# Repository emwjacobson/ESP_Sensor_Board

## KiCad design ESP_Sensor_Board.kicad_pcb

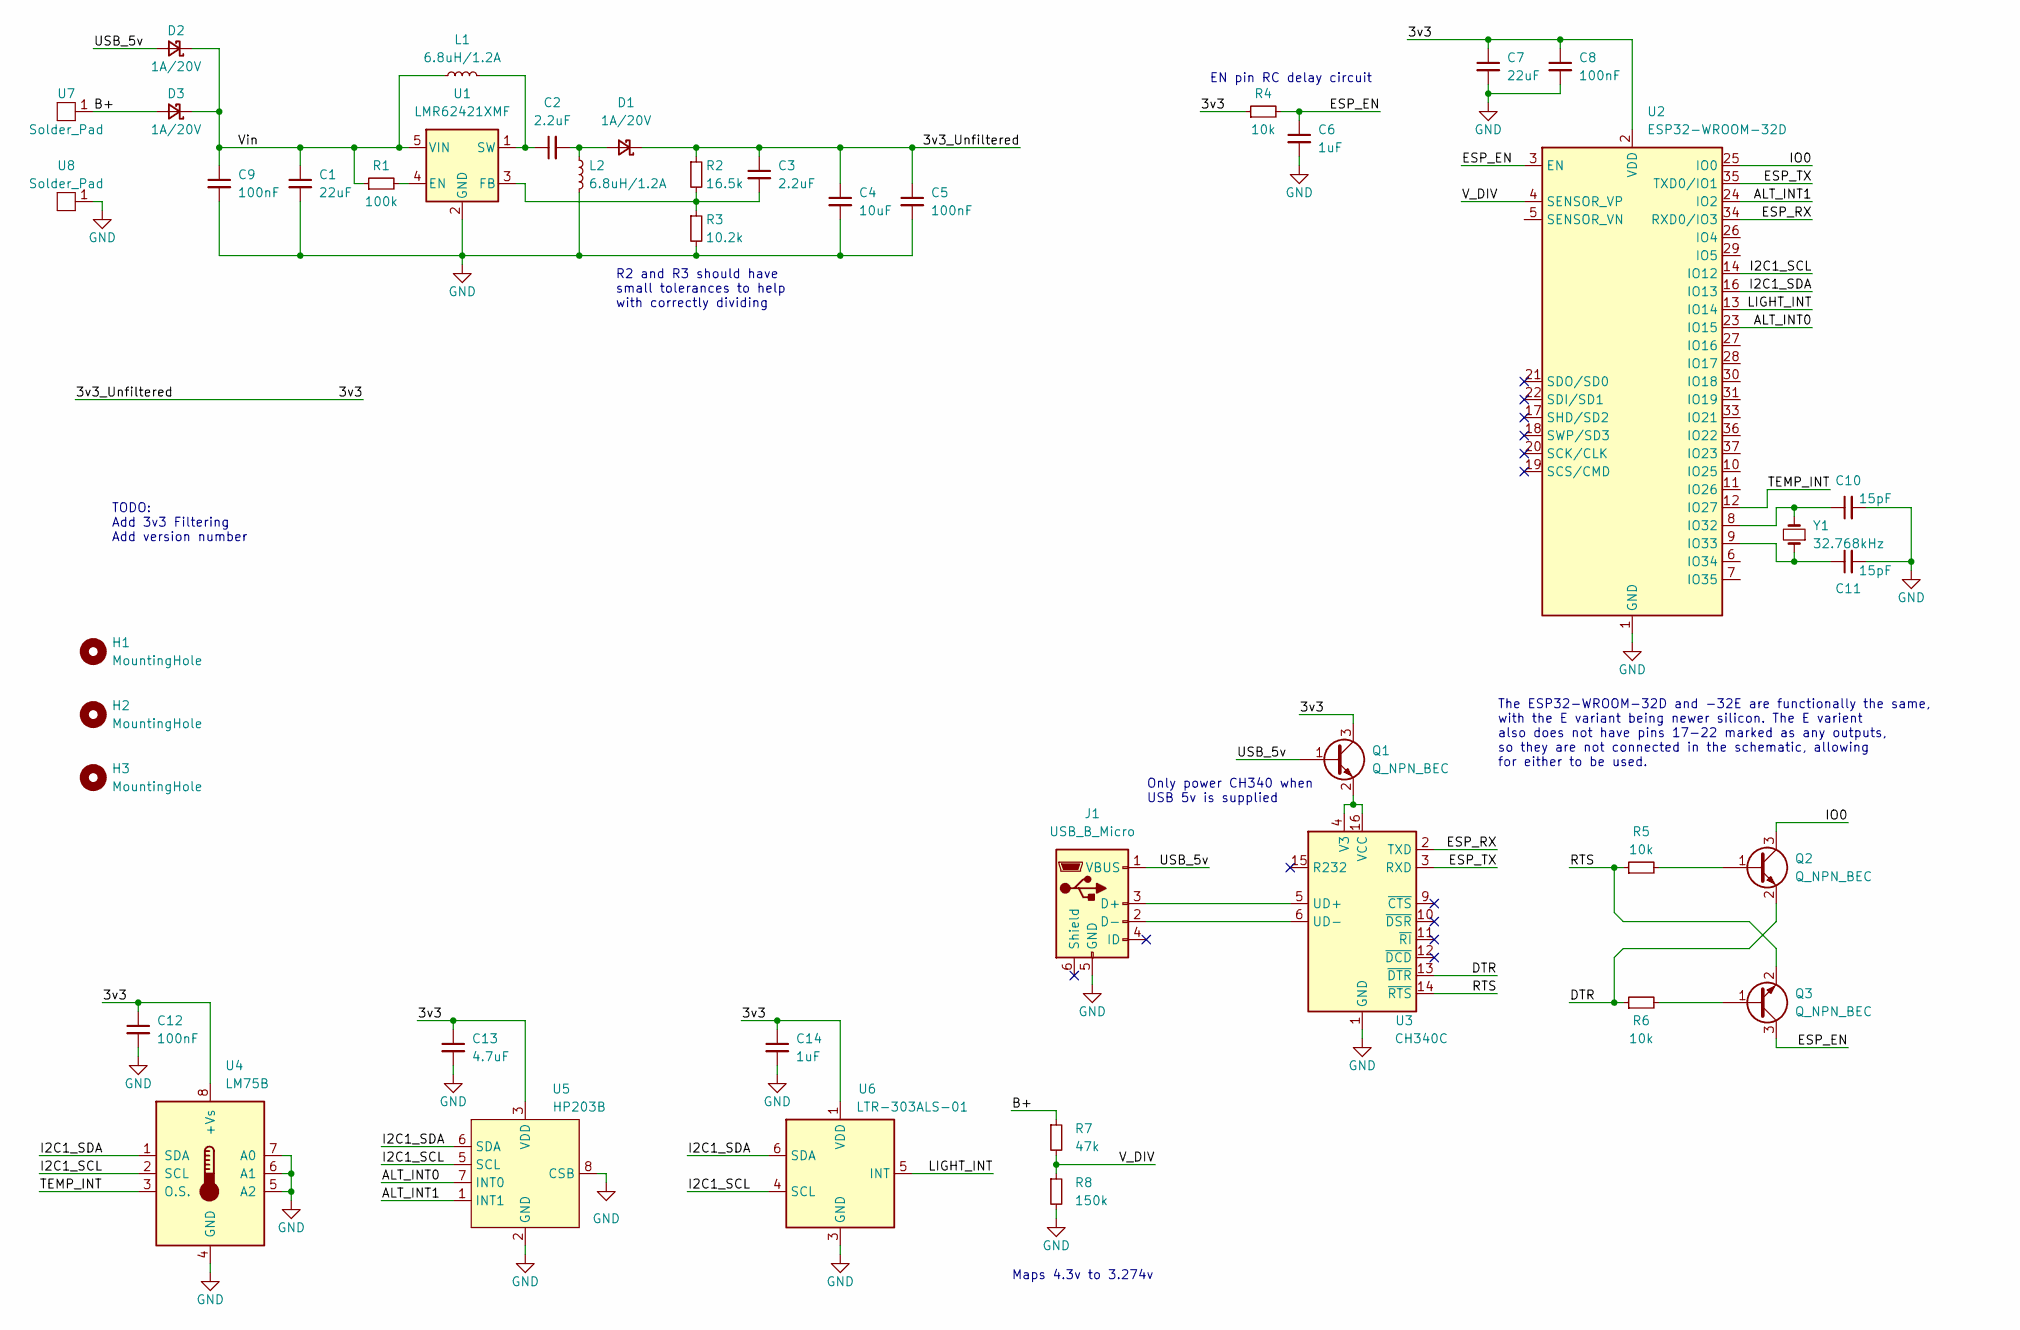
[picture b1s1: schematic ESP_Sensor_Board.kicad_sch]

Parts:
C1, C7: 22uF; C_0603_1608Metric; Manufacturer Part Number CL10A226MP8NUNE; LCSC Part Number C86295
C2, C3: 2.2uF; C_0603_1608Metric; Manufacturer Part Number CL10A225KO8NNNC; LCSC Part Number C23630
C4: 10uF; C_0603_1608Metric; Manufacturer Part Number CL10A106KP8NNNC; LCSC Part Number C19702
C5, C8, C9, C12: 100nF; C_0603_1608Metric; Manufacturer Part Number CL10B104KA8NNNC; LCSC Part Number C1590
C6, C14: 1uF; C_0603_1608Metric; Manufacturer Part Number CL10A105KO8NNNC; LCSC Part Number C1592
C10, C11: 15pF; C_0603_1608Metric; Manufacturer Part Number CL10C200JB8NNNC; LCSC Part Number C1648
C13: 4.7uF; C_0603_1608Metric; Manufacturer Part Number CL10A475KQ8NNNC; LCSC Part Number C8032
D1, D2, D3: 1A/20V; D_SOD-123F; Manufacturer Part Number DSS34; LCSC Part Number C511866
H1, H2, H3: MountingHole; MountingHole_3.2mm_M3
J1: USB_B_Micro; USB_Micro-B_Amphenol_10118194_Horizontal; Manufacturer Part Number 10118194-0001LF; LCSC Part Number C132563
L1, L2: 6.8uH/1.2A; L_4.5x3.2; Manufacturer Part Number CY43-6.8UH; LCSC Part Number C2929418
Q1, Q2, Q3: Q_NPN_BEC; SOT-23; Manufacturer Part Number SS8050; LCSC Part Number C2150
R1: 100k; R_0603_1608Metric; Manufacturer Part Number RC0603FR-07100KL; LCSC Part Number C14675
R2: 16.5k; R_0603_1608Metric; Manufacturer Part Number RC0603DR-0716K5L; LCSC Part Number C471802
R3: 10.2k; R_0603_1608Metric; Manufacturer Part Number RT0603DRE0710K2L; LCSC Part Number C706016
R4, R5, R6: 10k; R_0603_1608Metric; Manufacturer Part Number RT0603DRE0710KL; LCSC Part Number C706017
R7: 47k; R_0603_1608Metric; Manufacturer Part Number 0603WAF4702T5E; LCSC Part Number C25819
R8: 150k; R_0603_1608Metric; Manufacturer Part Number 0603WAF1503T5E; LCSC Part Number C22807
U1: LMR62421XMF; SOT-23-5; Manufacturer Part Number LMR62421XMF; LCSC Part Number C206031
U2: ESP32-WROOM-32D; ESP32-WROOM-32; Manufacturer Part Number ESP32-WROOM-32E(8MB); LCSC Part Number C701342
U3: CH340C; SOIC-16_3.9x9.9mm_P1.27mm; Manufacturer Part Number CH340C; LCSC Part Number C84681
U4: LM75B; MSOP-8_3x3mm_P0.65mm; Manufacturer Part Number LM75BDP; LCSC Part Number C2837470
U5: HP203B; Manufacturer Part Number HP203B; LCSC Part Number C138665
U6: LTR-303ALS-01; Lite-On_LTR-303ALS-01; Manufacturer Part Number LTR-303ALS-01; LCSC Part Number C364577
U7, U8: Solder_Pad; Pad
Y1: 32.768kHz; Crystal_SMD_3215-2Pin_3.2x1.5mm; Manufacturer Part Number X321532768KGD2SI; LCSC Part Number C620155

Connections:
/3v3: C3.1, C4.1, C5.1, C7.1, C8.1, C12.1, C13.1, C14.1, D1.1 (K), Q1.3 (C), R2.1, R4.1, U2.2 (VDD), U4.8 (+Vs), U5.3 (VDD), U6.1 (VDD)
/ALT_INT0: U2.23 (IO15), U5.7 (INT0)
/ALT_INT1: U2.24 (IO2), U5.1 (INT1)
/B+: D3.2 (A), R7.1, U7.1
/DTR: Q2.2 (E), R6.1, U3.13 (~DTR)
/ESP_EN: C6.1, Q3.3 (C), R4.2, U2.3 (EN)
/ESP_RX: U2.34 (RXD0/IO3), U3.2 (TXD)
/ESP_TX: U2.35 (TXD0/IO1), U3.3 (RXD)
/I2C1_SCL: U2.14 (IO12), U4.2 (SCL), U5.5 (SCL), U6.4 (SCL)
/I2C1_SDA: U2.16 (IO13), U4.1 (SDA), U5.6 (SDA), U6.6 (SDA)
/IO0: Q2.3 (C), U2.25 (IO0)
/LIGHT_INT: U2.13 (IO14), U6.5 (INT)
/RTS: Q3.2 (E), R5.1, U3.14 (~RTS)
/TEMP_INT: U2.12 (IO27), U4.3 (O.S.)
/USB_5v: D2.2 (A), J1.1 (VBUS), Q1.1 (B)
/V_DIV: R7.2, R8.1, U2.4 (SENSOR_VP)
/Vin: C1.1, C9.1, D2.1 (K), D3.1 (K), L1.1, R1.1, U1.5 (VIN)
GND: C1.2, C4.2, C5.2, C6.2, C7.2, C8.2, C9.2, C10.2, C11.2, C12.2, C13.2, C14.2, J1.5 (GND), L2.2, R3.2, R8.2, U1.2 (GND), U2.1 (GND), U2.15 (GND), U2.38 (GND), U2.39 (GND), U3.1 (GND), U4.4 (GND), U4.5 (A2), U4.6 (A1), U4.7 (A0), U5.2 (GND), U5.8 (CSB), U6.3 (GND), U8.1
unnamed: C2.1, L1.2, U1.1 (SW)
unnamed: C2.2, D1.2 (A), L2.1
unnamed: C3.2, R2.2, R3.1, U1.3 (FB)
unnamed: C10.1, U2.8 (IO32), Y1.2
unnamed: C11.1, U2.9 (IO33), Y1.1
unnamed: J1.2 (D-), U3.6 (UD-)
unnamed: J1.3 (D+), U3.5 (UD+)
unnamed: Q1.2 (E), U3.4 (V3), U3.16 (VCC)
unnamed: Q2.1 (B), R5.2
unnamed: Q3.1 (B), R6.2
unnamed: R1.2, U1.4 (EN)

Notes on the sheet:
Maps 4.3v to 3.274v
EN pin RC delay circuit
The ESP32-WROOM-32D and -32E are functionally the same, with the E variant being newer silicon. The E varient also does not have pins 17-22 marked as any outputs, so they are not connected in the schematic, allowing for either to be used.
TODO: Add 3v3 Filtering Add version number
Only power CH340 when USB 5v is supplied
R2 and R3 should have small tolerances to help with correctly dividing

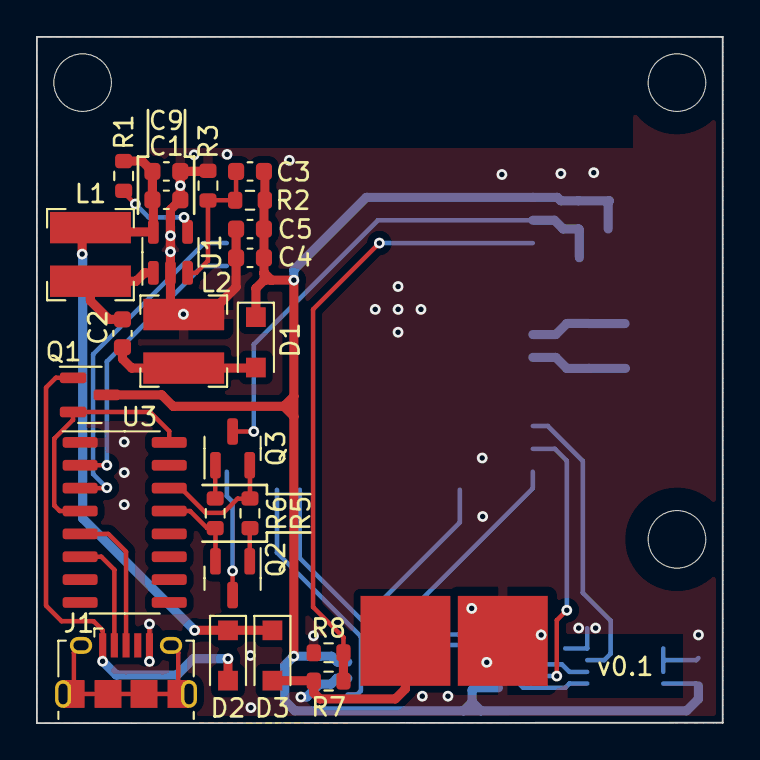
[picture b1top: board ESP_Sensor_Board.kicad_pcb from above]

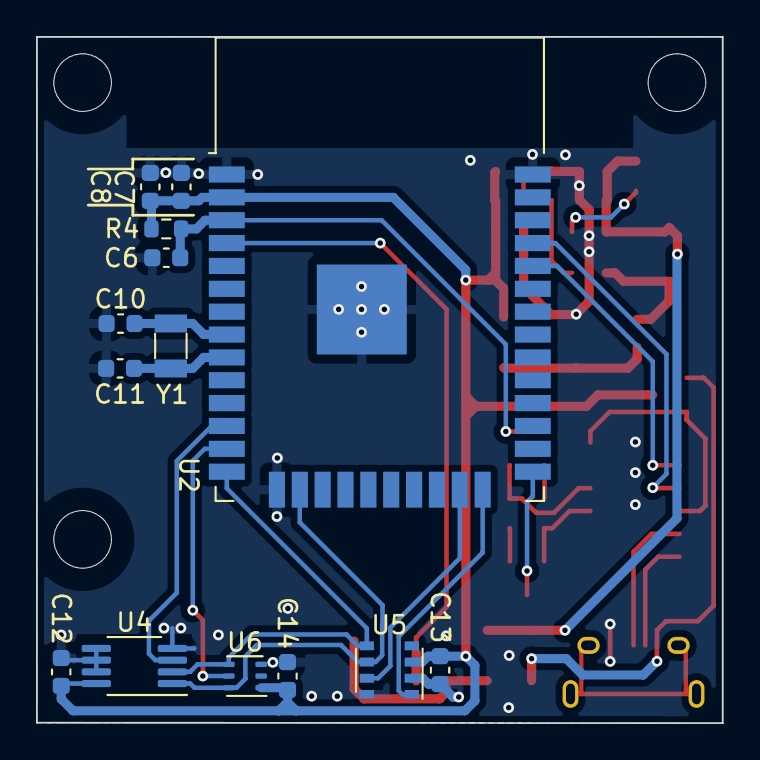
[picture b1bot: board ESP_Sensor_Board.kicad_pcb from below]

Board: 2 copper layers, 38.1 x 38.1 mm, 43 parts (14 on the bottom side), 29 nets.

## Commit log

2022-06-01 Started work adding voltage divider
2022-06-01 Moved sensors to back of board, added battery pads
